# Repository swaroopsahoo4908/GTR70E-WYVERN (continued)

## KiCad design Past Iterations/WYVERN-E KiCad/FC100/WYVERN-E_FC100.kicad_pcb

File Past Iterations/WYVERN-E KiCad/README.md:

# WYVERN-E KiCad Flight Computer Boards

| Project | Board | State |
|---|---|---|
| `FC100/WYVERN-E_FC100` | Ø92.1 mm round, 4 layers, for the 100 mm airframe | Rev 3.2, JLCPCBA release: 0 DRC violations (errors and warnings), 0 unconnected, 0 parity issues, ERC 0. Order files in `FC100/jlcpcb/` |
| `FC70/WYVERN-E_FC70` | Ø66.1 mm round, 4 layers, for the 70 mm airframe | Rev 3.2, JLCPCBA release: same checks all at 0. Order files in `FC70/jlcpcb/` |

Open either `.kicad_pro` in KiCad 10. Symbol and footprint libraries live inside each project.

## FC100 rev 3: JLCPCBA release

Rev 3 is FC100 re-issued for a turnkey JLCPCB assembly order. The schematic was corrected, the board re-placed and re-routed, and every placed part carries an LCSC number that was checked against JLCPCB's live assembly stock (JLCPCB parts API) on 2026-10-04. The order files are in `FC100/jlcpcb/`.

### What changed electrically

| # | Block | Rev 2 problem | Rev 3 fix | Source |
|---|---|---|---|---|
| 1 | USB-C / PD | CH224K (U2) was out of stock at JLC (0 pcs). Its VBUS pin was floating and its D+/D− shared the RP2350 USB pair. | U2 removed. CC1/CC2 get 5.1 kΩ Rd (R40, R41), so the board sinks plain 5 V at up to 3 A. The BQ25798 is a buck-boost, so it charges the 2S pack from 5 V with no PD needed. | CH224K datasheet; BQ25798 DS §8.3 |
| 2 | Charger | PROG R12 = 100 Ω (not in the PROG table) | R12 = 8.2 kΩ → 2S, 750 kHz | BQ25798 DS, PROG table |
| 3 | Charger | L4 3.3 µH | L4 2.2 µH FHD4020S-2R2MT (the 750 kHz value) | BQ25798 DS, inductor selection |
| 4 | Charger | TS had only the NTC to GND, so it would read "cold" and block charging | RT1 5.1 kΩ (REGN→TS), RT2 30 kΩ (TS→GND) with the 10 kΩ NTC R1 | BQ25798 DS, TS section |
| 5 | Charger | No VBUS, PMID, SYS or BAT capacitors besides C10 and one 100 nF | VBUS 2×10 µF + 100 nF, PMID 3×10 µF + 100 nF, SYS 3×10 µF + 100 nF + 10 µF at each buck input, BAT 2×10 µF (all 25 V X5R 0805) | BQ25798 DS §9.2.2 |
| 6 | Charger | BTST caps 100 nF | 47 nF, 50 V | BQ25798 DS |
| 7 | Charger LED | LED2 anode went to GND through R8, so it could never light | R8 (2.2 kΩ) now feeds LED2 from REGN, STAT sinks the cathode | — |
| 8 | 3V3 buck | TPS563201 EN floating. EN has an internal pull-down, so the 3V3 rail would never start. | EN tied to VSYS (EN abs max 19 V) | TPS563201 DS |
| 9 | 3V3 buck | No output capacitors; FB 330k/100k | 2×22 µF out; FB 33k/10k → 3.302 V | TPS563201 DS table 7-2 |
| 10 | Servo buck | L3 2.2 µH (TI table says 15 µH at 5 V/500 kHz), no output caps, FB 748k/100k | L3 10 µH SWPA6045 (Isat 3.5 A), 2×22 µF out, 75 pF feed-forward, FB (47k+27k)/10k → 5.006 V | TPS54202 DS table 7-2 |
| 11 | RP2350 | PSRAM CS on GPIO33. QMI CS1n only exists on GPIO0/8/19/47, so the PSRAM was unreachable. | PSRAM_CS → GPIO47, U32 pin 3 → GPIO40/ADC0. The other GPIO functions moved in the pin swap (see `fc100_board.h`). | RP2350 DS, GPIO function table |
| 12 | RP2350 | VREG_AVDD direct to 3V3, no 4.7 µF on VREG_VIN or DVDD, 1 µH core inductor | 33 Ω + 4.7 µF AVDD filter, 4.7 µF on VREG_VIN and DVDD, L1 = 3.3 µH Abracon AOTA-B201610S3R3 | Hardware design with RP2350 |
| 13 | RP2350 | No USB series resistors | 27 Ω on D+/D− at the MCU (R42, R43) | Hardware design with RP2350 |
| 14 | RP2350 | 12 MHz HC-49 crystal, 18 pF, no drive limiting | ABM8-272-T3 (the reference crystal), 15 pF, 1 kΩ in XOUT | Hardware design with RP2350 |
| 15 | RP2350 | No BOOTSEL button | U35 + 1 kΩ on QSPI_SS | Hardware design with RP2350 |
| 16 | RP2350 | W25Q32JVSSIQ: 1 pc in stock | W25Q128JVSIQ (16 MB, JLC Basic, same SOIC-8 208 mil) | — |
| 17 | Status LED | LED1 anode to GND, cathode to GPIO via R9, so it could never light | LED1 anode via 330 Ω from GPIO32, cathode to GND: active high | — |
| 18 | INA226 | U8 and U9 both A0=A1=GND → both 0x40 | U9 A0 → VS → 0x41. ALERT pins left open (they were shorted to GND). | INA226 DS address table |
| 19 | ADAU1450 | DVDD (1.2 V) pins had only C35 bulk | 4×100 nF on DVDD pins 20/35/53/71 plus 100 nF on each IOVDD, AVDD and PVDD | ADAU1450 DS |
| 20 | LSM9DS1 | CAP pin 100 nF | 10 nF | ST LSM9DS1 DS §4.1 |
| 21 | Decoupling | Sensors and memories had no local cap | 100 nF at U6, U7, U8, U9, U10, U11, U12, U13, U14 (×2), U15 (×2), U17; 10 µF at the microSD socket | — |
| 22 | Charger | Bootstrap caps were cross-wired: C17 (BTST1) sat on SW2 and C18 (BTST2) on SW1. The high-side gate drives would have been referenced to the wrong switch node. | C17: BTST1→SW1, C18: BTST2→SW2, 47 nF each | BQ25798 DS pin table |
| 23 | USB | D+/D− were shared three ways (USB-C, RP2350, BQ25798 BC1.2 detection) | BQ25798 D+/D− left open, so the pair runs point-to-point. Firmware sets the input limit over I²C instead. | — |

ILIM_HIZ tied to REGN is correct and stays. VILIM_HIZ = 1 V + 0.8 Ω·IINDPM, so REGN (5 V) gives the hardware maximum. HIZ only happens below 0.75 V. The rev 2 note that called it an HIZ bug was wrong. The input limit is set in firmware (REG06).

### FC100 rev 3 status

| Check | Result |
|---|---|
| ERC | 0 violations |
| DRC errors (clearance, short, hole, edge, thermal, courtyard) | 0 |
| Open connections | 0 |
| Schematic ↔ PCB parity | 0 issues |
| DRC warnings left | 0 (rev 3.2 silkscreen clean-up) |
| Parts | 166 placed (all top side): 165 assembled + TP1 (bare SWD pad, DNP), plus 4 mounting holes |
| Copper | 2,611 track segments; 533 vias; 40 zones |
| BOM | 64 lines, 165 placements, every line has an LCSC number |

### Routing, layers, widths

| Layer | Use | Cu |
|---|---|---|
| F.Cu | parts, signals, GND pour, high-current pours | 1 oz |
| In1.GND_SIG | GND pour, with short signal escapes under the RP2350/ADAU1450 where the pour flows around them | 0.5 oz |
| In2.SIG_PWR | signals + +3V3 pour | 0.5 oz |
| B.Cu | signals, GND pour, high-current pours | 1 oz |

Stackup JLC04161H-7628, 1.6 mm. Order it as 4 layers, 1.6 mm, ENIG, "specified stackup: JLC04161H-7628".

| Class | Routed / widened to | Clearance | Via | Notes |
|---|---|---|---|---|
| Default (logic) | 0.10–0.15 mm | 0.10 mm | 0.5 / 0.3 mm | JLC multilayer standard capability is 0.09/0.09 mm, so 0.10/0.10 is inside the no-surcharge envelope |
| Power (+3V3, +1V1, +1V2_DSP, REGN, VREG, GND) | up to 0.5 mm | 0.127 mm | 0.5 / 0.3 mm | +3V3 also on the In2 pour; GND on three pours |
| HighCurrent (VBAT, VBUS, VSYS, PMID, SW nodes, VSERVO, pyro outputs) | up to 1.5 mm + priority-5 copper pours hugging every track | 0.15 mm | 0.8 / 0.4 mm | Routed on outer layers only |
| USB | 0.25–0.28 mm, point-to-point USB-C ↔ 27 Ω ↔ RP2350 | 0.10 mm | 0.5 / 0.3 mm | Full-speed 12 Mb/s |

The BQ25798 power stage is hand-placed and pre-routed in the TI EVM pattern: L4 sits directly over the PMID/SW1/GND/SW2/SYS bars, PMID caps on the left, SYS caps on the right, VBUS and BAT caps below them. The GND bar drops straight into three vias between the inductor pads, and pins 10/11/13/27 join under the package (the RQM package has no exposed pad). The RP2350 got a 1.3 mm escape ring with no parts in it.

GPIO pin swap: every freely assignable GPIO (H1 header, 9 servo outputs, aux header, interrupts, LED, card-detect, PDM audio) was re-assigned to the RP2350B pin nearest its destination. This is a Hungarian assignment on pad distance, and it cut total wirelength from 1001 mm to 769 mm. Nets are now named by function (`SERVO_U19`, `HDR_P1`…). `firmware/fc100_bringup/fc100_board.h` is generated from the netlist by `tools/gen_fwpins.py`, so code and copper can't drift apart.

### JLCPCB order

1. PCB: upload `FC100/jlcpcb/WYVERN-E_FC100_gerbers.zip` (Gerbers + Excellon, PTH and NPTH separate). Options: 4 layers, 1.6 mm, JLC04161H-7628, ENIG. Use "Via covering: epoxy filled & capped" (POFV) if you can, because the RP2350/ADAU1450 exposed pads and a few QFN-adjacent pads have vias in them. Plain tented is the fallback; expect slightly more solder voiding on the EPs.
2. Assembly: top side, upload `WYVERN-E_FC100_BOM.csv` and `WYVERN-E_FC100_CPL.csv`. The CPL is in the Gerber coordinate frame (aux origin at the board's bottom-left corner), rotations 0–359°. EasyEDA-origin footprints carry JLC's own orientation. The KiCad-library ones were corrected (SOT-223 +180°).
3. In the placement preview, check these by eye before confirming: U34 (AMS1117, tab up), L1 (AOTA inductor, polarity dot toward VREG_LX, i.e. toward U1), LED1/LED2 (cathode marks), D1/D2, U3/U1/U18 pin-1 dots.
4. Through-hole parts are in the BOM with LCSC numbers (C10, CN1, H1, U19–U33 connectors). Keep them for JLC's THT assembly, or untick them and hand-solder.
5. The cost estimate at 2026-10-04 prices is about $77/board in parts. 40 of the 64 lines are JLC "extended" parts (about $3 setup each, per order).

Stock is thin on three parts, enough for a prototype run: LPS22HBTR 51 pcs, LSM9DS1TR 71, ADAU1450 79. Everything else is in the hundreds or more. Check again on the day you order.

### 3D models

Every assembled part (165 of 165) carries its manufacturer 3D model, pulled from the LCSC/EasyEDA library for its exact LCSC number. Only TP1 (bare test pad) and the four mounting holes have none, by design.

- Models live in `FC100/3dmodels/` (STEP) and are referenced as `${KIPRJMOD}/3dmodels/…`, so they travel with the project. The project footprint library has the same model links, so "Update footprints from library" keeps them.
- Alignment was computed per footprint, not trusted blindly. Each model's pads were matched to the board footprint's pads to get rotation and offset (the SOT-223 needed 180°). EasyEDA's STEP files were checked against their VRML twins, and 14 had origin shifts (Z on the passives, XY on the 1×4 headers, microSD socket, USB-C and JST-XH), which were corrected. The PSRAM (USON-8) only had a VRML model, so it was converted to STEP.
- `FC100/WYVERN-E_FC100.step` is the full assembled board (all 165 models, no copper) for mechanical fit checks in the airframe CAD.
- Renders: `FC100/renders/*_3d_top.png`, `*_3d_bottom.png`, `*_3d_iso.png`.

### USB-C access (rev 3.1)

USBC1 (TYPE-C-31-M-12, C165948) was moved 3.13 mm toward the board edge. Before the move its receptacle face sat 2.2–2.7 mm inside the 92 mm outline, so the board edge stopped a standard plug overmold before it seated.

- Receptacle face is now at y = 53.67 mm. The outline's closest point under the plug (x = 100) is at 54.00, so the shell overhangs the edge by 0.33 mm at the center and up to 0.9 mm at the left corner, and nothing on the board sits in the plug's path.
- The plug overmold (USB-IF max 12.35 × 8.25 mm) clears both tact switches (U35 BOOTSEL, U16 RUN) and the H1 header, all of which sit behind the receptacle face.
- Routing was dragged with the connector. Three GND stitching vias under the new shell position were removed, the VBUS escape was re-jogged to clear shell leg 2, and the shell-to-R41 GND stub was replaced by a GND via at (91.48, 61.50). DRC: 0 errors, 0 unconnected; ERC 0; parity clean.
- The USB-C 3D model was also fixed. add3d had it 2.4 mm behind its footprint, and it is now pinned at offset (0, −2.448, 0), rotation 180°, with shell legs on their pads.
- In the CPL, only USBC1's Y changed (84.1984 → 87.3284 mm).
- Airframe: the port faces radially outward at the 12 o'clock position of the top view (≈3.4° left of the +Y axis, board-center bearing). It needs an airframe or sled cut-out of at least 14 × 10 mm, centered 1.6 mm above the top copper (receptacle centerline).

## Firmware

`firmware/fc100_bringup/`:

- `fc100_board.h`: the full pin map and every I²C address, generated from the KiCad netlist.
- `fc100_bringup.ino` (arduino-pico): probes both I²C buses against the expected address list, configures the BQ25798 (watchdog off, AUTO_INDET off, 1.0 A charge, 1.5 A input limit, ADC on) and reads VBUS/VBAT/VSYS, reads both INA226s, checks the 8 MB PSRAM on GPIO47, and mounts the SD card.

Run it before the flight code. The current `wyvern4_tvc` firmware targets the Pico 2 W perfboard (BNO085s on GP0/GP1, servos on GP2/GP3), so it needs this header swapped in: sensors are on I2C0 = GPIO12/13 and the system bus on I2C1 = GPIO14/15. The BQ25798 register addresses in the sketch are from the TI register map. Confirm them against section 9.5 of the datasheet before the first powered run.

Flashing: hold BOOTSEL (U35), tap RUN (U16), then drop the UF2. SWD is on H1 pin 14 (SWDIO) and test pad TP1 (SWCLK).

## Regenerating

`tools/` holds the full pipeline (Python 3, KiCad 10 pcbnew, Freerouting 2.1): EasyEDA parser → schematic (`run_sch.py cfg100 geom`) → floorplan placement (`place.py`) → stage/pre-route (`route_stage.py`) → Freerouting → `finalize.py` → repair/rip-up (`targeted.py`, `repair2.py`, `polish3.py`) → `widenonly.py`, `hcpour.py`, `zonecfg.py`, `tidy.py` → `jlc_export.py`. `jlc.py` queries JLCPCB's parts API for stock and Basic/Extended status. The configs reference the extracted EasyEDA files by absolute path, so edit `epru=` in `cfg100.py`/`cfg70.py` before re-running. FC70 rev 3 uses `cfg70r3.py`. The rev 3.2 clean-up scripts are `silk2.py` (silkscreen), `bottleneck.py` (current-path check), `dfm.py` (JLC capability audit), `collide.py` (3D body overlap), `widennet.py`/`splitnet.py`/`addvias.py` (power copper).

## FC70 rev 3: JLCPCBA release

FC70 got the same treatment as FC100: corrected schematic, LCSC part numbers checked against JLCPCB's live stock (2026-10-09, every line in stock), a new floorplan, and a full re-route.

### Schematic fixes

| # | Rev 2 problem | Rev 3 fix | Source |
|---|---|---|---|
| 1 | RP2350 VREG: three 4.7 µF on AVDD, none on VREG_VIN | C4/C5 moved to the 3V3 input, 4.7 µF on AVDD after the 33 Ω, 4.7 µF on DVDD | Raspberry Pi, *Hardware design with RP2350*, §2.3 |
| 2 | Too few IOVDD bypass caps for 8 IOVDD pins | C36–C39 added (100 nF each) | same |
| 3 | No HF bypass at either TPS564201 VIN | C40, C41 100 nF next to VIN/GND | TI TPS564201 DS §8.2.2.4 |
| 4 | AP2112K input had no local cap | C42 1 µF | Diodes AP2112 DS |
| 5 | BNO055 BL_IND (an output) tied to GND | Left unconnected | Bosch BNO055 DS, table 5-1 |
| 6 | microSD shell floating, no card detect | Shell tabs to GND, CD to GPIO13 | Hroparts TF-01A drawing |
| 7 | USB-C shell and JST-SH tabs floating | Tied to GND | |
| 8 | Servo PWM on pins far from the servo connectors | SERVO1–4 on GPIO41/39/38/40 (four separate PWM channels, facing the connectors) | RP2350 DS, PWM table |
| 9 | 12 MHz crystal ~40 mm from the RP2350, XIN not even connected | Crystal next to XIN/XOUT, routed | |
| 10 | No 10 µF bulk at the microSD socket | C35 10 µF | |
| 11 | Slide switch U13 was on LCSC C2884744 (SS-12D10G5, 4.7 mm pitch, 1.7 mm holes) while the footprint is SS12D00G3 (2.5 mm pitch) | Changed to C22355741 SS-12D00-G3, which matches the footprint | LCSC listing |

The firmware pin map is generated from the netlist: `firmware/fc70_pins/fc70_board.h`.

### FC70 JLCPCB order

Same procedure as FC100, using `FC70/jlcpcb/`: 4 layers, 1.6 mm, JLC04161H-7628, ENIG; top-side assembly with `WYVERN-E_FC70_BOM.csv` and `WYVERN-E_FC70_CPL.csv` (aux origin at the bottom-left corner). Through-hole parts with LCSC numbers: XT30 (CN1), four JST-XH servo connectors (U8–U11), H1/H2 headers, slide switch U13. Lowest stock on 2026-10-09 was the AOTA 3.3 µH (L1) at 134 pcs and the 1×14 header at 488. In the placement preview, check L1's polarity dot, D1/D2 cathodes, the TPS564201 (U6/U15) and RP2350 pin-1 dots.

All 95 assembled FC70 parts carry LCSC/EasyEDA STEP models in `FC70/3dmodels/`, checked by exporting each part and comparing its body to its pads; `FC70/WYVERN-E_FC70.step` is the assembled board.

### FC70 layout notes

- USB-C receptacle face sits 0.10 mm past the outline at its closest point, so the plug overmold never touches the board. The fan-out between the 0.5 mm-pitch pads uses a 0.10 mm clearance rule that only applies inside the USBC1 and D1 courtyards (JLC minimum is 0.09 mm).
- Battery path: the XT30 feeds the 10 mΩ shunt through a 1.8 mm bottom-layer bar plus the original top route, with five 0.3 mm vias into the shunt pad.
- Servo buck switch node rebuilt: 0.7–1.2 mm from U6 pin 2 to L3. Its EN line was moved out from under the IC.
- High-current nets have local pours (`HC_*` zones) over their tracks on F.Cu.

## Rev 3.2 checks (both boards, 2026-10-09)

All numbers below are from the files in this package.

| Check | FC100 | FC70 | JLCPCB 4-layer capability |
|---|---|---|---|
| DRC errors / warnings / unconnected / parity | 0 / 0 / 0 / 0 | 0 / 0 / 0 / 0 | |
| ERC errors / warnings | 0 / 0 | 0 / 0 | |
| Min track | 0.10 mm (71 QFN escape segments, rest ≥ 0.127) | 0.15 mm | 0.09 mm |
| Min clearance | 0.10 mm (fine-pitch rules, scoped to courtyards) | 0.10 mm (same) | 0.09 mm |
| Vias | 0.5/0.3, 0.6/0.3, 0.8/0.4 mm | 0.5/0.3, 0.6/0.3, 0.8/0.4 mm | 0.3 mm hole is the no-surcharge size |
| Min via annular ring | 0.10 mm | 0.10 mm | — |
| Min PTH drill / ring | 0.8 mm / 0.20 mm | 0.8 mm / 0.20 mm | — |
| Silkscreen | 0.15 mm lines, refs 1.0 mm (0.8 mm where tight) | same | 0.153 mm line, 0.8 mm text |
| Placed parts with LCSC # / in stock | 165 / 165 | 95 / 95 | |
| 3D bodies overlapping each other | 0 | 0 | |

### Silkscreen

`tools/silk2.py` re-placed every reference designator:

- Outline segments that crossed pads were clipped.
- A ref only goes on silk if it sits next to its own part and clearly closer to it than to any other part. Big parts carry their ref inside the body.
- Refs that can't meet that go to the Fab layer, so the assembly drawing still has them.
- No silk touches a pad, another legend or the board edge.

### Current capacity

`tools/bottleneck.py` finds the widest copper path between the pads that actually carry power. It counts tracks, pours and vias, and ignores the first 2.5 mm at each pin. The design currents are realistic flight loads: 3.5 A battery, 3 A servo rail, 3 A USB. Pass mark is the IPC-2221 external-layer width for a 20 °C rise.

| Path | Narrowest copper | Status |
|---|---|---|
| FC100 USB VBUS → charger caps | 0.5 mm (A-side), 1.5 mm main run | Short necks at the 0.5 mm-pitch connector; most of the 33 mm run along the edge was widened from 0.2 to 1.2–1.5 mm (0.5 mm past the BOOTSEL switch) |
| FC100 VBAT charger ↔ shunt | 4 vias in parallel + pours | OK |
| FC100 VSYS → servo buck | 4 vias + 2.9 mm pour | OK |
| FC100 servo rail branches | 0.2 mm necks ≤ 2.4 mm long (between connector pins and past C57) | Fine for one servo per branch (≈1 A). It is the one place on either board where a long 2-servo stall could warm the trace; nothing larger fit there. |
| FC70 battery → shunt | 1.8 mm B.Cu bar + 5 vias | OK |
| FC70 shunt → servo PTC | 3–4 vias each end + 1.0 mm | OK |
| FC70 servo buck SW / VSERVO | 2.6 mm / 3.0 mm pours | OK |

Narrow tracks that remain on these nets are Kelvin sense lines to the INA226s and bootstrap-cap links, which carry microamps to milliamps.

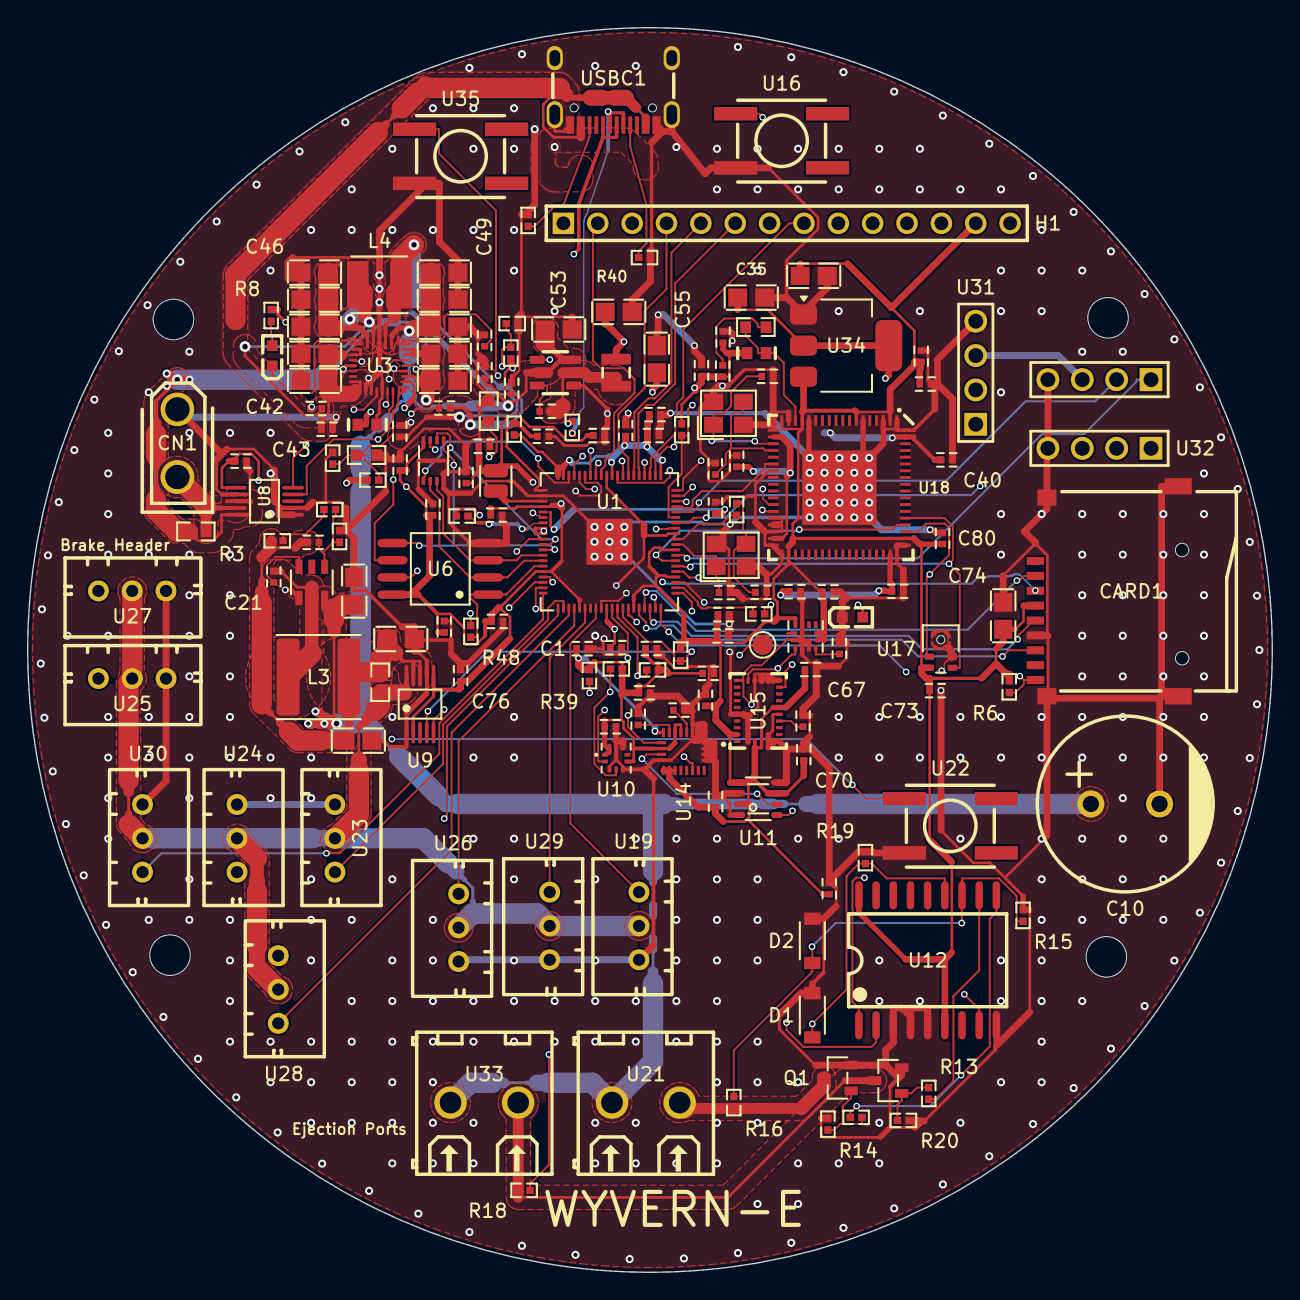
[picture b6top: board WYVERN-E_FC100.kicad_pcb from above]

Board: 4 copper layers, 92.0 x 92.0 mm, 170 parts (0 on the bottom side), 114 nets.

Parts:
C1, C11, C12, C13, C14, C16, C19, C20, C21, C22, C24, C25, C26, C27, C28, C29, C30, C31, C32, C33, C37, C38, C39, C40, C43, C50, C63, C64, C65, C66, C67, C68, C69, C70, C71, C72, C73, C75, C76, C77, C78, C79, C80, C81, C82: 100nF; C0402
C2, C3: 15pF; C0402
C4, C5: 18pF; C0402
C6: 1nF 50V; C0402
C7: 4.7uF 16V; C0603
C8: 150pF NP0; C0603
C9: 5.6nF; C0402
C10: 2200uF 25V; CAP-TH_BD13.0-P5.00-D1.2-FD
C17, C18: 47nF 50V; C0402
C23: 10nF; C0402
C35, C55, C56, C57, C58: 22uF; C0805
C36, C41, C42, C44, C45, C46, C47, C48, C49, C51, C52, C53, C54, C74: 10uF; C0805
C59: 75pF; C0402
C60, C61, C62: 4.7uF; C0402
CARD1: TF-01A; TF-SMD_TF-01A
CN1: XT30UPB-M; CONN-TH_XT30UPB-M
D1, D2: BZT52C3V3; SOD-123_L2.7-W1.6-LS3.7-RD
H1: 2011-1X14G00SB; HDR-TH_14P-P2.54-V-M_4
L1: 3.3uH; L_Wuerth_PMFI-201610
L2: 2.2uH; IND-SMD_L2.5-W2.0_MHCHL2520
L3: 10uH; L_Sunlord_SWPA6045S
L4: 2.2uH; IND-SMD_L4.0-W4.0
LED1, LED2: KT-0603R; LED-SMD_L1.6-W0.8-R-RD
MH1, MH2, MH3, MH4: MountingHole
Q1, Q2: AO3400A; SOT-23-3_L2.9-W1.3-P1.90-LS2.4-BR
R1: 10k NTC; R0603
R2, R16, R18: 33k; R0402
R3, R7: 10mΩ; R0603
R4: 47k; R0402
R5: 27k; R0402
R6: 20k; R0402
R8: 2.2k; R0402
R9: 330; R0402
R10: 4.3k; R0603
R11, R13, R47, R48: 1k; R0402
R12: 8.2k; R0603
R14, R15, R17, R19, R20, R31, R32: 10k; R0402
R36, R37, R38, R39: 4.7k; R0402
R40, R41, R44: 5.1k; R0402
R42, R43: 27; R0402
R45: 30k; R0402
R46: 33; R0402
TP1: SWCLK; TestPoint_Pad_D1.5mm
U1: RP2350B; QFN-80_L10.0-W10.0-P0.40-TL-EP3.4
U3: BQ25798RQMR; QFN-29_L4.0-W4.0-P0.40-TL-BQ25792RQMR
U4: TPS563201DDCR; SOT-23-6_L2.9-W1.6-P0.95-LS2.8-BR
U5: TPS54202DDCR; SOT-23-6_L2.9-W1.6-P0.95-LS2.8-BL
U6: W25Q128JVSIQ; SOIC-8_L5.3-W5.3-P1.27-LS8.0-BL
U7: APS6404L-3SQR-ZR; USON-8_L3.0-W2.0-P0.50-BL-EP
U8, U9: INA226AIDGSR; MSOP-10_L3.0-W3.0-P0.50-LS5.0-BL
U10: LPS22HBTR; HLGA-10L_LPS22HBTR
U11: BME680; LGA-8_L3.0-W3.0-P0.80-TR
U12: MCP23008-E/SO; SOIC-18_L11.6-W7.5-P1.27-LS10.3-BL
U13: LIS3MDLTR; LGA-12_L2.0-W2.0-P0.50-BL
U14: LSM9DS1TR; LGA-24_L3.5-W3.0-P0.43-TL
U15: BNO055; LGA-28_L5.2-W3.8-P0.50-BL
U16, U22: EVQ-Q2P02W; SW-SMD_4P-L6.5-W6.0-P4.00-LS6.6-TL
U17: IM63D135AXTMA1; MIC-SMD_5P-L3.5-W2.7_IM66D130AXTMA1
U18: ADAU1450WBCPZ-RL; LFCSP-72_L10.0-W9.8-P0.50-LS10.2-TL-EP5.5
U19, U23, U24, U25, U26, U27, U28, U29, U30: B3B-XH-A(LF)(SN); CONN-TH_3P-P2.50_A2501WV2-3P
U20, U31, U32: 2.54-1*4; HDR-TH_4P-P2.54-V-M-1
U21, U33: KF128-5.0-2P; CONN-TH_P5.00_KF128-5.0-2P
U34: AMS1117-1.2; SOT-223-3_TabPin2
U35: BOOTSEL; SW-SMD_4P-L6.5-W6.0-P4.00-LS6.6-TL
USBC1: TYPE-C-31-M-12; USB-C_SMD-TYPE-C-31-M-12_1
X1: 12MHz; CRYSTAL-SMD_4P-L3.2-W2.5-BL
X2: 12.288MHz; CRYSTAL-SMD_4P-L3.2-W2.5-BL

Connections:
+1V1_DVDD: C11.1, C12.1, C13.1, C14.1, C62.1, L1.2, U1.10, U1.32, U1.51, U1.65
+1V2_DSP: C35.1, C37.1, C38.1, C39.1, C40.1, U18.20, U18.35, U18.53, U18.71, U34.2
+3V3: C1.1, C8.1, C9.1, C16.1, C26.1, C27.1, C28.1, C29.1, C30.1, C31.1, C32.1, C33.1, C36.1, C55.1, C56.1, C61.1, C63.1, C64.1, C65.1, C66.1, C67.1, C68.1, C69.1, C70.1, C71.1, C72.1, C73.1, C74.1, C75.1, C76.1, C77.1, C78.1, C79.1, C80.1, C81.1, C82.1, CARD1.4, H1.13, L2.2, R2.1, R6.2, R17.2, R36.2, R37.2, R38.2, R39.2, R46.1, U1.5, U1.15, U1.24, U1.29, U1.41, U1.50, U1.59, U1.60, U1.64, U1.68, U1.69, U1.76, U6.8, U7.8, U8.6, U9.2, U9.6, U10.1, U10.6, U10.10, U11.2, U11.6, U11.8, U12.6, U12.18, U13.5, U13.6, U13.10, U14.1, U14.3, U14.6, U14.7, U14.8, U14.22, U14.23, U15.3, U15.4, U15.11, U15.28, U17.1, U18.2, U18.7, U18.15, U18.18, U18.38, U18.56, U20.3, U31.3, U34.3
AUX_P1: U1.28, U20.1
AUX_P2: U1.36, U20.2
BOOTSEL_SW: R48.2, U35.1
BQ_PROG: R12.1, U3.20
BQ_REGN: C7.1, R8.2, R44.1, U3.5, U3.17
BQ_SW1: C17.2, L4.2, U3.28
BQ_SW2: C18.2, L4.1, U3.26
BUCK3V3_FB: R2.2, R31.1, U4.4
BUCK3V3_SW: C20.2, L2.1, U4.2
BUCKSV_FB: C59.2, R5.2, R32.1, U5.4
BUCKSV_SW: C21.2, L3.1, U5.2
BUCK_SV_FB_MID: R4.2, R5.1
DSP_LRCLK: U1.27, U18.58
DSP_PLLFILT: C8.2, R10.1, U18.16
DSP_RESET: U1.37, U18.24
DSP_XTALIN: C5.1, U18.21, X2.1
DSP_XTALOUT: C4.1, U18.22, X2.3
GND: C1.2, C2.2, C3.2, C4.2, C5.2, C6.2, C7.2, C10.2, C11.2, C12.2, C13.2, C14.2, C16.2, C19.2, C22.2, C23.2, C24.2, C25.2, C26.2, C27.2, C28.2, C29.2, C30.2, C31.2, C32.2, C33.2, C35.2, C36.2, C37.2, C38.2, C39.2, C40.2, C41.2, C42.2, C43.2, C44.2, C45.2, C46.2, C47.2, C48.2, C49.2, C50.2, C51.2, C52.2, C53.2, C54.2, C55.2, C56.2, C57.2, C58.2, C60.2, C61.2, C62.2, C63.2, C64.2, C65.2, C66.2, C67.2, C68.2, C69.2, C70.2, C71.2, C72.2, C73.2, C74.2, C75.2, C76.2, C77.2, C78.2, C79.2, C80.2, C81.2, C82.2, CARD1.6, CARD1.10, CARD1.11, CARD1.12, CARD1.13, CN1.1, D1.2, D2.2, LED1.2, Q1.2, Q2.2, R1.2, R12.2, R14.2, R15.2, R19.2, R20.2, R31.2, R32.2, R40.2, R41.2, R45.2, U1.62, U1.81, U3.10, U3.11, U3.13, U3.27, U4.1, U5.1, U6.4, U7.4, U7.9, U8.1, U8.2, U8.7, U9.1, U9.7, U10.3, U10.5, U10.8, U10.9, U11.1, U11.5, U11.7, U12.3, U12.4, U12.5, U12.9, U13.2, U13.3, U13.9, U13.12, U14.5, U14.14, U14.15, U14.16, U14.17, U14.18, U14.19, U14.20, U15.2, U15.5, U15.6, U15.10, U15.15, U15.16, U15.17, U15.18, U15.25, U16.3, U17.4, U17.5, U18.1, U18.3, U18.6, U18.14, U18.17, U18.19, U18.25, U18.32, U18.33, U18.34, U18.36, U18.37, U18.54, U18.55, U18.72, U18.73, U19.3, U20.4, U22.3, U23.3, U24.3, U25.3, U26.3, U27.3, U28.3, U29.3, U30.3, U31.4, U32.4, U34.1, U35.3, USBC1.1, USBC1.2, USBC1.3, USBC1.4, USBC1.A1B12, USBC1.B1A12, X1.2, X1.4, X2.2, X2.4
GPIO40_ADC0: U1.49, U32.3
GPIO43_ADC3: U1.54, U31.1
GPIO44_ADC4: U1.55, U31.2
GPIO45_ADC5: U1.56, U32.1
GPIO46_ADC6: U1.57, U32.2
HDR_P1: H1.1, U1.53
HDR_P2: H1.2, U1.52
HDR_P3: H1.3, U1.48
HDR_P4: H1.4, U1.47
HDR_P5: H1.5, U1.46
HDR_P6: H1.6, U1.45
HDR_P7: H1.7, U1.44
HDR_P8: H1.8, U1.43
HDR_P9: H1.9, U1.42
HDR_P10: H1.10, U1.40
HDR_P11: H1.11, U1.39
HDR_P12: H1.12, U1.38
I2C0_SCL_SENS: R37.1, U1.12, U10.2, U11.4, U13.1, U14.2, U15.19
I2C0_SDA_SENS: R36.1, U1.11, U10.4, U11.3, U13.11, U14.4, U15.20
I2C1_SCL: R39.1, U1.14, U3.14, U8.5, U9.5, U12.1, U18.31
I2C1_SDA: R38.1, U1.13, U3.15, U8.4, U9.4, U12.2, U18.30
LED1_A: LED1.1, R9.2
LED1_DRV: R9.1, U1.22
LED2_A: LED2.1, R8.1
Net-C9-Pad2: C9.2, R10.2
Net-C22-Pad1: C22.1, U13.4
Net-C24-Pad1: C24.1, U14.24
PDM_CLK: U1.25, U17.2, U18.57
PDM_DATA: U1.26, U17.3, U18.59
PSRAM_CS: U1.58, U7.1
PYRO1_CONT: D2.1, R15.1, R16.2, U12.12
PYRO1_DRV: R11.1, U12.10
PYRO1_GATE: Q1.1, R11.2, R14.1
PYRO1_OUT: Q1.3, R16.1, U21.2
PYRO2_CONT: D1.1, R18.2, R19.1, U12.13
PYRO2_DRV: R13.1, U12.11
PYRO2_GATE: Q2.1, R13.2, R20.1
PYRO2_OUT: Q2.3, R18.1, U33.2
QSPI_SCLK: U1.71, U6.6, U7.6
QSPI_SD0: U1.72, U6.5, U7.5
QSPI_SD1: U1.74, U6.2, U7.2
QSPI_SD2: U1.73, U6.3, U7.3
QSPI_SD3: U1.70, U6.7, U7.7
QSPI_SS_FLASH: R48.1, U1.75, U6.1
RUN: R17.1, U1.35, U16.1
SD_CD: CARD1.9, R6.1, U1.23
SD_CS: CARD1.2, U1.17
SD_MISO: CARD1.7, U1.16
SD_MOSI: CARD1.3, U1.19
SD_SCK: CARD1.5, U1.18
SERVO_U19: U1.8, U19.1
SERVO_U23: U1.2, U23.1
SERVO_U24: U1.1, U24.1
SERVO_U25: U1.79, U25.1
SERVO_U26: U1.4, U26.1
SERVO_U27: U1.78, U27.1
SERVO_U28: U1.3, U28.1
SERVO_U29: U1.6, U29.1
SERVO_U30: U1.80, U30.1
SWCLK: TP1.1, U1.33
SWDIO: H1.14, U1.34
U3_BTST1: C17.1, U3.4
U3_BTST2: C18.1, U3.19
U3_INT: U1.77, U3.21
U3_PMID: C19.1, C44.1, C45.1, C46.1, U3.29
U3_QON: U3.12, U22.1
U3_SDRV: C6.1, U3.24
U3_STAT: LED2.2, U3.1
U3_TS: R1.1, R44.2, R45.1, U3.16
U4_VBST: C20.1, U4.6
U5_BOOT: C21.1, U5.6
U12_INT: U1.20, U12.8
U14_CAP: C23.1, U14.21
U14_NT1_A: U1.9, U14.11
U15_CAP: C25.1, U15.9
U15_INT: U1.21, U15.14
USBC_CC1: R40.1, USBC1.A5
USBC_CC2: R41.1, USBC1.B5
USB_DN: R43.1, USBC1.A7, USBC1.B7
USB_DN_MCU: R43.2, U1.66
USB_DP: R42.1, USBC1.A6, USBC1.B6
USB_DP_MCU: R42.2, U1.67
VBAT: C51.1, C52.1, R3.1, U3.18, U3.22, U3.23, U8.8, U8.10
VBAT_RAW: CN1.2, R3.2, U8.9
VBUS: C41.1, C42.1, C43.1, U3.2, U3.3, U3.8, U3.9, USBC1.A4B9, USBC1.B4A9
VREG_AVDD: C60.1, R46.2, U1.61
VREG_LX: L1.1, U1.63
VSERVO: R7.1, U9.10, U19.2, U23.2, U24.2, U25.2, U26.2, U27.2, U28.2, U29.2, U30.2
VSERVO_PRE: C57.1, C58.1, C59.1, L3.2, R4.1, R7.2, U9.8, U9.9
VSYS: C10.1, C47.1, C48.1, C49.1, C50.1, C53.1, C54.1, U3.25, U4.3, U4.5, U5.3, U21.1, U33.1
XIN: C2.1, U1.30, X1.1
XOUT: R47.1, U1.31
XOUT_X: C3.1, R47.2, X1.3

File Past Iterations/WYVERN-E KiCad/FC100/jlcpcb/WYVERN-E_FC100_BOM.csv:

Comment,Designator,Footprint,LCSC Part #,Manufacturer Part,Quantity
100nF,"C1,C11,C12,C13,C14,C16,C19,C20,C21,C22,C24,C25,C26,C27,C28,C29,C30,C31,C32,C33,C37,C38,C39,C40,C43,C50,C63,C64,C65,C66,C67,C68,C69,C70,C71,C72,C73,C75,C76,C77,C78,C79,C80,C81,C82",C0402,C1525,CL05B104KO5NNNC,45
15pF,"C2,C3",C0402,C1548,0402CG150J500NT,2
18pF,"C4,C5",C0402,C1549,0402CG180J500NT,2
1nF 50V,C6,C0402,C1523,0402B102K500NT,1
4.7uF 16V,C7,C0603,C19666,CL10A475KO8NNNC,1
150pF NP0,C8,C0603,C107038,CC0603JRNPO9BN151,1
5.6nF,C9,C0402,C281760,CC0402KRX7R9BB562,1
2200uF 25V,C10,CAP-TH_BD13.0-P5.00-D1.2-FD,C44598,KM228M025J20RR0VH2FP0,1
47nF 50V,"C17,C18",C0402,C82219,0402B473K500NT,2
10nF,C23,C0402,C15195,CL05B103KB5NNNC,1
22uF,"C35,C55,C56,C57,C58",C0805,C45783,CL21A226MAQNNNE,5
10uF,"C36,C41,C42,C44,C45,C46,C47,C48,C49,C51,C52,C53,C54,C74",C0805,C15850,CL21A106KAYNNNE,14
75pF,C59,C0402,C107010,CC0402JRNPO9BN750,1
4.7uF,"C60,C61,C62",C0402,C23733,CL05A475MP5NRNC,3
TF-01A,CARD1,TF-SMD_TF-01A,C91145,TF-01A,1
XT30UPB-M,CN1,CONN-TH_XT30UPB-M,C428721,XT30UPB-M,1
BZT52C3V3,"D1,D2",SOD-123_L2.7-W1.6-LS3.7-RD,C173413,BZT52C3V3,2
2011-1X14G00SB,H1,HDR-TH_14P-P2.54-V-M_4,C49569637,2011-1X14G00SB,1
3.3uH,L1,L_Wuerth_PMFI-201610,C42411119,AOTA-B201610S3R3-101-T,1
2.2uH,L2,IND-SMD_L2.5-W2.0_MHCHL2520,C5832372,FTC252012S2R2MBCA,1
10uH,L3,L_Sunlord_SWPA6045S,C79272,SWPA6045S100MT,1
2.2uH,L4,IND-SMD_L4.0-W4.0,C602029,FHD4020S-2R2MT,1
KT-0603R,"LED1,LED2",LED-SMD_L1.6-W0.8-R-RD,C2286,KT-0603R,2
AO3400A,"Q1,Q2",SOT-23-3_L2.9-W1.3-P1.90-LS2.4-BR,C20917,AO3400A,2
10k NTC,R1,R0603,C13564,NCP18XH103F03RB,1
33k,"R2,R16,R18",R0402,C25779,0402WGF3302TCE,3
10mΩ,"R3,R7",R0603,C158899,RTT03R010FTP,2
47k,R4,R0402,C25792,0402WGF4702TCE,1
27k,R5,R0402,C25771,0402WGF2702TCE,1
20k,R6,R0402,C25765,0402WGF2002TCE,1
2.2k,R8,R0402,C25879,0402WGF2201TCE,1
330,R9,R0402,C25104,0402WGF3300TCE,1
4.3k,R10,R0603,C23159,0603WAF4301T5E,1
1k,"R11,R13,R47,R48",R0402,C11702,0402WGF1001TCE,4
8.2k,R12,R0603,C25981,0603WAF8201T5E,1
10k,"R14,R15,R17,R19,R20,R31,R32",R0402,C25744,0402WGF1002TCE,7
4.7k,"R36,R37,R38,R39",R0402,C25900,0402WGF4701TCE,4
5.1k,"R40,R41,R44",R0402,C25905,0402WGF5101TCE,3
27,"R42,R43",R0402,C25156,0402WGJ0270TCE,2
30k,R45,R0402,C138008,RC0402FR-0730KL,1
33,R46,R0402,C25105,0402WGF330JTCE,1
RP2350B,U1,QFN-80_L10.0-W10.0-P0.40-TL-EP3.4,C42415655,RP2350B,1
BQ25798RQMR,U3,QFN-29_L4.0-W4.0-P0.40-TL-BQ25792RQMR,C2876593,BQ25798RQMR,1
TPS563201DDCR,U4,SOT-23-6_L2.9-W1.6-P0.95-LS2.8-BR,C116592,TPS563201DDCR,1
TPS54202DDCR,U5,SOT-23-6_L2.9-W1.6-P0.95-LS2.8-BL,C191884,TPS54202DDCR,1
W25Q128JVSIQ,U6,SOIC-8_L5.3-W5.3-P1.27-LS8.0-BL,C97521,W25Q128JVSIQ,1
APS6404L-3SQR-ZR,U7,USON-8_L3.0-W2.0-P0.50-BL-EP,C3040877,APS6404L-3SQR-ZR,1
INA226AIDGSR,"U8,U9",MSOP-10_L3.0-W3.0-P0.50-LS5.0-BL,C49851,INA226AIDGSR,2
LPS22HBTR,U10,HLGA-10L_LPS22HBTR,C94049,LPS22HBTR,1
BME680,U11,LGA-8_L3.0-W3.0-P0.80-TR,C125972,BME680,1
MCP23008-E/SO,U12,SOIC-18_L11.6-W7.5-P1.27-LS10.3-BL,C92253,MCP23008-E/SO,1
LIS3MDLTR,U13,LGA-12_L2.0-W2.0-P0.50-BL,C478483,LIS3MDLTR,1
LSM9DS1TR,U14,LGA-24_L3.5-W3.0-P0.43-TL,C2655096,LSM9DS1TR,1
BNO055,U15,LGA-28_L5.2-W3.8-P0.50-BL,C93216,BNO055,1
EVQ-Q2P02W,"U16,U22,U35",SW-SMD_4P-L6.5-W6.0-P4.00-LS6.6-TL,C2680625,EVQ-Q2P02W,3
IM63D135AXTMA1,U17,MIC-SMD_5P-L3.5-W2.7_IM66D130AXTMA1,C41574995,IM63D135AXTMA1,1
ADAU1450WBCPZ-RL,U18,LFCSP-72_L10.0-W9.8-P0.50-LS10.2-TL-EP5.5,C654399,ADAU1450WBCPZ-RL,1
B3B-XH-A(LF)(SN),"U19,U23,U24,U25,U26,U27,U28,U29,U30",CONN-TH_3P-P2.50_A2501WV2-3P,C144394,B3B-XH-A(LF)(SN),9
2.54-1*4,"U20,U31,U32",HDR-TH_4P-P2.54-V-M-1,C5116483,2.54-1*4,3
KF128-5.0-2P,"U21,U33",CONN-TH_P5.00_KF128-5.0-2P,C474950,KF128-5.0-2P,2
AMS1117-1.2,U34,SOT-223-3_TabPin2,C347218,AMS1117-1.2,1
TYPE-C-31-M-12,USBC1,USB-C_SMD-TYPE-C-31-M-12_1,C165948,TYPE-C-31-M-12,1
12MHz,X1,CRYSTAL-SMD_4P-L3.2-W2.5-BL,C20625731,ABM8-272-T3,1
12.288MHz,X2,CRYSTAL-SMD_4P-L3.2-W2.5-BL,C519811,NX3225GA-12.288MHz-STD-CRG-2,1

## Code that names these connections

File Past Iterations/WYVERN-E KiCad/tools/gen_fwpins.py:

"""Generate fc100_board.h from the KiCad netlist (_design.json + symbol pin names)."""
import json,re,sys
d=json.load(open('/tmp/w/out/FC100/_design.json'))
sym=open('/tmp/w/out/FC100/WYVERN_FC100.kicad_sym').read()
i=sym.find('(symbol "RP2350B'); j=sym.find('\n(symbol "',i+1)
pn={n:nm for nm,n in re.findall(r'\(name "([^"]*)".*?\(number "([^"]*)"',sym[i:j])}
gp={}
for k,net in d['nets'].items():
    r,n=k.split('.',1)
    if r!='U1': continue
    m=re.match(r'GPIO(\d+)',pn.get(n,''))
    if m: gp[net]=int(m.group(1))
def g(net): return gp[net]
servo=['SERVO_U19','SERVO_U23','SERVO_U24','SERVO_U25','SERVO_U26','SERVO_U27','SERVO_U28','SERVO_U29','SERVO_U30']
hdr=[f'HDR_P{i}' for i in range(1,13)]
o=[]
w=o.append
w('#pragma once')
w('// =================================================================================================')
w('// WYVERN-E FC-100 rev 3 (JLCPCBA release) -- board pin map for arduino-pico (earlephilhower core).')
w('// GENERATED from the KiCad netlist by tools/gen_fwpins.py. Do not hand-edit: re-run after any schematic change.')
w('// Target: RP2350B QFN-80. 16 MB W25Q128 on QMI CS0, 8 MB APS6404L PSRAM on QMI CS1.')
w('// Board menu: "Generic RP2350", Flash 16MB, PSRAM 8MB, PSRAM CS = %d (or -DRP2350_PSRAM_CS=%d).' % (g('PSRAM_CS'),g('PSRAM_CS')))
w('// =================================================================================================')
w('')
w('// ---- I2C0: sensor bus')
w(f"#define FC_I2C0_SDA        {g('I2C0_SDA_SENS')}")
w(f"#define FC_I2C0_SCL        {g('I2C0_SCL_SENS')}      // 4.7k pull-ups R36/R37")
for n,a,c in [('LIS3MDL',0x1C,'SA1 = GND'),('LSM9DS1_M',0x1E,'SDO_M = 3V3'),('BNO055',0x28,'COM3 = GND'),('LPS22HB',0x5C,'SA0 = GND'),('LSM9DS1_AG',0x6A,'SDO_A/G = GND'),('BME680',0x76,'SDO = GND')]:
    w(f"#define FC_ADDR_{n:<11}0x{a:02X}    // {c}")
w('')
w('// ---- I2C1: system bus')
w(f"#define FC_I2C1_SDA        {g('I2C1_SDA')}")
w(f"#define FC_I2C1_SCL        {g('I2C1_SCL')}      // 4.7k pull-ups R38/R39")
for n,a,c in [('MCP23008',0x20,'A2..A0 = GND'),('ADAU1450',0x38,'ADDR1/0 = GND, SELFBOOT = GND (host loads program over I2C)'),('INA_BATT',0x40,'U8, 10 mOhm R3 in the pack lead'),('INA_SERVO',0x41,'U9, A0 = VS, 10 mOhm R7 in VSERVO'),('BQ25798',0x6B,'charger')]:
    w(f"#define FC_ADDR_{n:<11}0x{a:02X}    // {c}")
w('#define FC_INA_SHUNT_OHM   0.010f')
w('')
w('// ---- microSD on SPI0')
w(f"#define FC_SD_MISO         {g('SD_MISO')}      // SPI0 RX")
w(f"#define FC_SD_CS           {g('SD_CS')}")
w(f"#define FC_SD_SCK          {g('SD_SCK')}")
w(f"#define FC_SD_MOSI         {g('SD_MOSI')}      // SPI0 TX")
w(f"#define FC_SD_CD           {g('SD_CD')}      // card detect, 20k pull-up R6")
w('')
w('// ---- servo / actuator outputs, JST-XH 3P (SIG, VSERVO 5.0 V, GND). Order = connector reference order.')
w('// U19, U23, U24, U25, U26, U27, U28, U29, U30. Every RP2350 GPIO has a PWM channel.')
w('static const uint8_t FC_SERVO_PINS[9] = {' + ', '.join(str(g(s)) for s in servo) + '};')
w(f"#define FC_SERVO_PITCH     {g('SERVO_U19')}      // U19")
w(f"#define FC_SERVO_YAW       {g('SERVO_U23')}      // U23")
w('')
w('// ---- H1 1x14 header: pins 1..12 = GPIO below, pin 13 = 3V3, pin 14 = SWDIO. SWCLK on test pad TP1.')
w('static const uint8_t FC_HDR_PINS[12] = {' + ', '.join(str(g(h)) for h in hdr) + '};  // H1 pin 1..12')
w(f"// U20 1x4: GPIO{g('AUX_P1')}, GPIO{g('AUX_P2')}, 3V3, GND")
w(f"#define FC_AUX1            {g('AUX_P1')}")
w(f"#define FC_AUX2            {g('AUX_P2')}")
w(f"// U31 1x4: GPIO{g('GPIO43_ADC3')} (ADC3), GPIO{g('GPIO44_ADC4')} (ADC4), 3V3, GND")
w(f"// U32 1x4: GPIO{g('GPIO45_ADC5')} (ADC5), GPIO{g('GPIO46_ADC6')} (ADC6), GPIO{g('GPIO40_ADC0')} (ADC0), GND")
w('')
w('// ---- status, interrupts, audio')
w(f"#define FC_LED1            {g('LED1_DRV')}      // active HIGH, 330R")
w(f"#define FC_MCP_INT         {g('U12_INT')}")
w(f"#define FC_DSP_RESET       {g('DSP_RESET')}      // ADAU1450 RESET, active LOW")
w(f"#define FC_PDM_CLK         {g('PDM_CLK')}      // IM63D135 CLK + ADAU1450 BCLK_IN0 (PIO-driven)")
w(f"#define FC_PDM_DATA        {g('PDM_DATA')}      // IM63D135 DATA (L/R = GND) + ADAU1450 SDATA_IN0")
w(f"#define FC_DSP_LRCLK       {g('DSP_LRCLK')}      // ADAU1450 LRCLK_IN0")
w(f"#define FC_LSM9DS1_INT1    {g('U14_NT1_A')}")
w(f"#define FC_BNO055_INT      {g('U15_INT')}")
w(f"#define FC_BQ_INT          {g('U3_INT')}      // open drain: enable the internal pull-up")
w(f"#define FC_PSRAM_CS        {g('PSRAM_CS')}      // QMI CS1n (only GPIO0/8/19/47 can carry it)")
w('')
w('// ---- MCP23008 pyro channels (recovery is motor ejection; keep disarmed unless deliberately used)')
w('#define FC_MCP_PYRO1_DRV   0       // GP0 -> 1k -> AO3400A Q1 gate, 10k pull-down')
w('#define FC_MCP_PYRO2_DRV   1')
w('#define FC_MCP_PYRO1_CONT  2       // GP2 <- 33k/10k divider from channel output, 3V3 zener clamp')
w('#define FC_MCP_PYRO2_CONT  3')
w('')
w('// ---- power (rev 3): USB-C 5 V (5.1k Rd, no PD) or 2S pack (XT30) -> BQ25798 (PROG 8.2k: 2S, 750 kHz)')
w('//      -> VSYS -> TPS563201 3V3 (EN tied to VSYS) and TPS54202 VSERVO 5.0 V; AMS1117-1.2 for ADAU1450 DVDD.')
w('#define FC_VBAT_WARN_V     6.4f')
w('#define FC_VBAT_CRIT_V     6.0f')
open(sys.argv[1],'w').write('\n'.join(o)+'\n')
print('ok',len(gp))
